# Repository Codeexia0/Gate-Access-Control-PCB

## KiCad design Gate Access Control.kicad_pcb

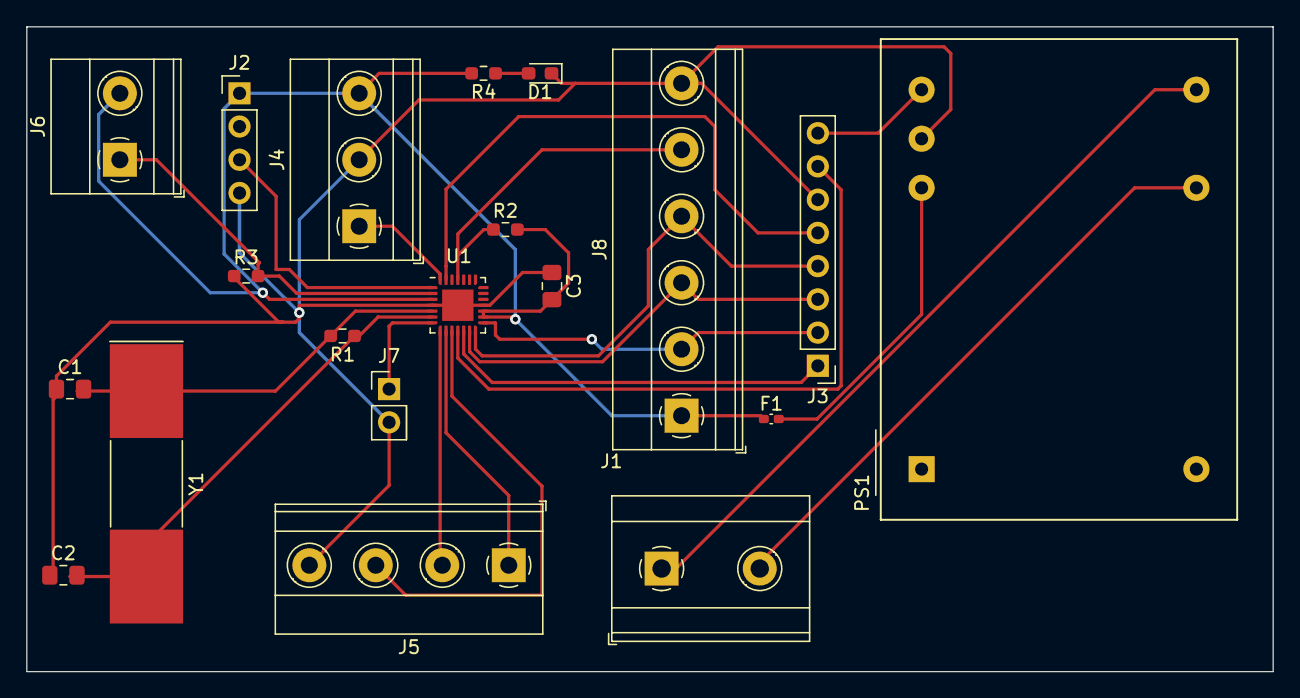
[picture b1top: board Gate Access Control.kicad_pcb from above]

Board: 2 copper layers, 95.2 x 49.3 mm, 20 parts (0 on the bottom side), 23 nets.

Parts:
C1, C2: 22pF; C_0805_2012Metric_Pad1.18x1.45mm_HandSolder
C3: 100nF; C_0805_2012Metric_Pad1.18x1.45mm_HandSolder
D1: LED; LED_0603_1608Metric_Pad1.05x0.95mm_HandSolder
F1: 200 mA; Fuse_0402_1005Metric_Pad0.77x0.64mm_HandSolder
J1: Screw_Terminal_01x02; TerminalBlock_MetzConnect_Type175_RT02702HBLC_1x02_P7.50mm_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
J2: RF Receiver 433MHz; PinHeader_1x04_P2.54mm_Vertical
J3: Conn_01x08; PinHeader_1x08_P2.54mm_Vertical
J4: IR_SENSORT; TerminalBlock_Phoenix_MKDS-1,5-3-5.08_1x03_P5.08mm_Horizont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
J5: Screw_Terminal_01x04; TerminalBlock_Phoenix_MKDS-1,5-4-5.08_1x04_P5.08mm_Horizont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
J6: Screw_Terminal_01x02; TerminalBlock_Phoenix_MKDS-1,5-2-5.08_1x02_P5.08mm_Horizont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
J7: Conn_01x02; PinHeader_1x02_P2.54mm_Vertical
J8: Screw_Terminal_01x06; TerminalBlock_Phoenix_MKDS-1,5-6-5.08_1x06_P5.08mm_Horizont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
PS1: TMLM04253; Converter_ACDC_TRACO_TMLM-04_THT
R1, R2: 1M; R_0603_1608Metric_Pad0.98x0.95mm_HandSolder
R3: 10k; R_0603_1608Metric_Pad0.98x0.95mm_HandSolder
R4: 220R; R_0603_1608Metric_Pad0.98x0.95mm_HandSolder
U1: ATmega328-MM; QFN-28-1EP_4x4mm_P0.45mm_EP2.4x2.4mm
Y1: Crystal; Crystal_SMD_SeikoEpson_MA505-2Pin_12.7x5.1mm_HandSoldering

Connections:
+3.3V: J3.8, PS1.4 (Vout2)
+5V: C3.2, F1.1, J2.1 (VCC), J4.3 (VCC), J6.2, J8.1, R2.2, R4.2, U1.3 (VCC), U1.16 (AVCC), U1.17 (AREF)
/DXN: J5.3, U1.10 (PB0)
/Enable: J5.1, U1.9 (PD7)
/Flashing Lights: J7.1, U1.7 (PD5)
/IR Sensor - DI: J4.1 (DATA), U1.28 (PD2)
/IRQ: J3.5, U1.27 (PD1)
/Inverter PWM: J5.2, U1.8 (PD6)
/MISO: J3.4, J8.4, U1.14 (PB4)
/MOSI: J3.3, J8.3, U1.13 (PB3)
/RESET: J8.5, R2.1, U1.25 (~RESET/PC6)
/RF receiver - PWM: J2.3 (DATA), U1.1 (PD3)
/RST: J3.7, U1.11 (PB1)
/SCK: J3.2, J8.2, U1.15 (PB5)
/SDA/SS: J3.1, U1.12 (PB2)
/Switch IN: J6.1, R3.2, U1.2 (PD4)
/XTAL1: C1.2, R1.2, U1.5 (XTAL1/PB6), Y1.1
/XTAL2: C2.2, R1.1, U1.6 (XTAL2/PB7), Y1.2
GND: C1.1, C2.1, C3.1, D1.1 (K), J2.4 (GND), J3.6, J4.2 (GND), J5.4, J7.2, J8.6, PS1.3 (Common), R3.1, U1.4 (GND), U1.18 (GND), U1.29 (GND)
unnamed: D1.2 (A), R4.1
unnamed: J1.1, PS1.5 (AC(L))
unnamed: J1.2, PS1.6 (AC(N))
unnamed: F1.2, PS1.2 (Vout1)

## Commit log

2023-12-17 PCB first try
    Designed pcb using vias so it is double sided pcb
